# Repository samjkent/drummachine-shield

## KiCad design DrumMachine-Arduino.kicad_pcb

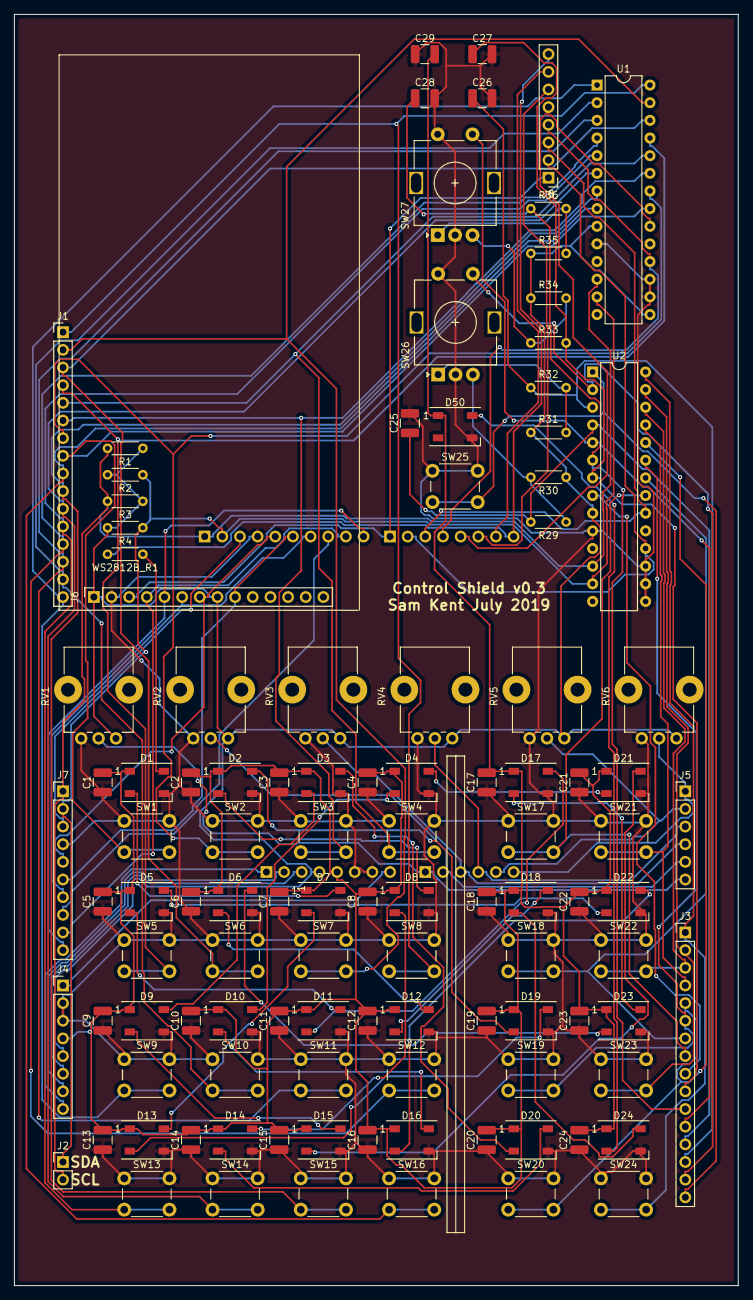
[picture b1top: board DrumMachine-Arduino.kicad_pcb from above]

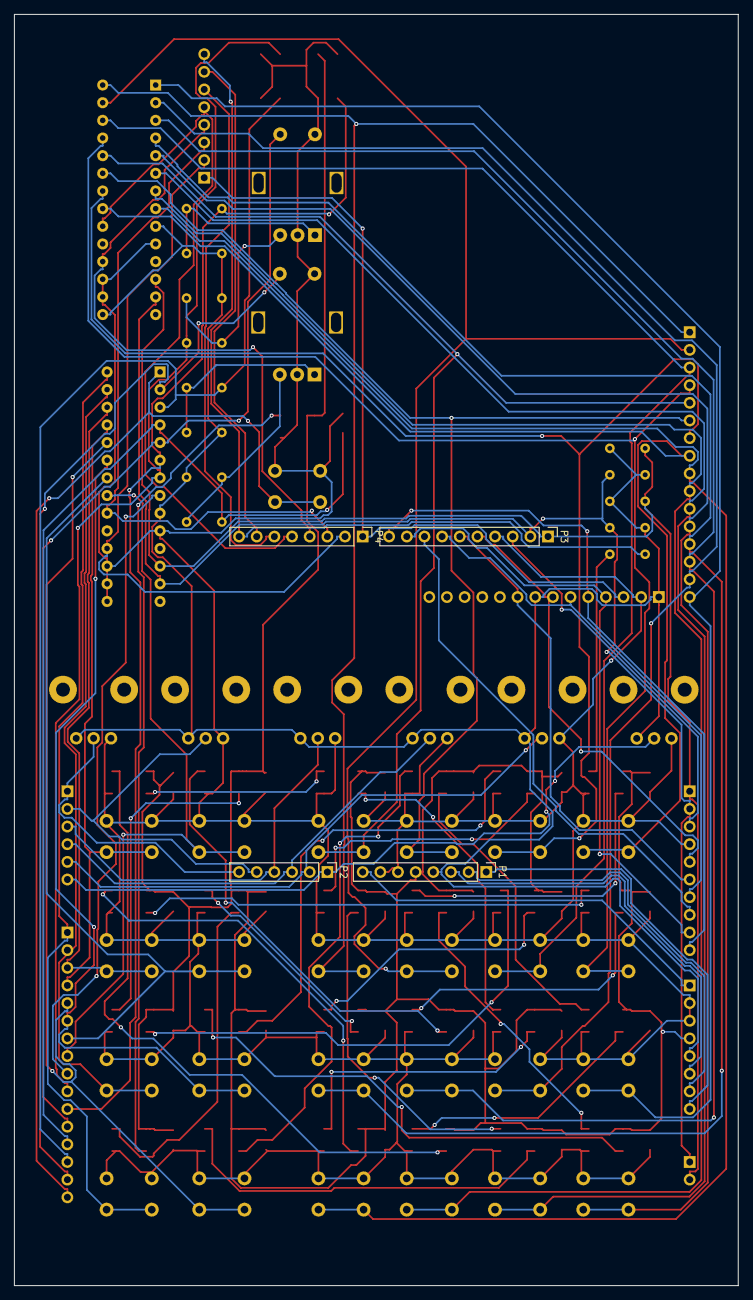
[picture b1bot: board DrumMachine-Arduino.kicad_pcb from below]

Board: 2 copper layers, 104.1 x 182.9 mm, 114 parts (4 on the bottom side), 91 nets.

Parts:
C1, C2, C3, C4, C5, C6, C7, C8, C9, C10, C11, C12, C13, C14, C15, C16, C17, C18, C19, C20, C21, C22, C23, C24, C25, C26, C27, C28, C29: C; C_1210_3225Metric
D1, D2, D3, D4, D5, D6, D7, D8, D9, D10, D11, D12, D13, D14, D15, D16, D17, D18, D19, D20, D21, D22, D23, D24, D50: WS2812B; LED_WS2812B_PLCC4_5.0x5.0mm_P3.2mm
J1, J3: Conn_01x16_Female; PinHeader_1x16_P2.54mm_Vertical
J2: I2C_BUS; PinHeader_1x02_P2.54mm_Vertical
J4, J8: Conn_01x08_Female; PinHeader_1x08_P2.54mm_Vertical
J5: Conn_01x06_Female; PinHeader_1x06_P2.54mm_Vertical
J6: DISPLAY; PinSocket_1x14_P2.54mm_Vertical_Display
J7: Conn_01x10_Female; PinHeader_1x10_P2.54mm_Vertical
P1: Power; PinHeader_1x08_P2.54mm_Vertical
P2: Analog; PinHeader_1x06_P2.54mm_Vertical
P3: Digital; PinHeader_1x10_P2.54mm_Vertical
P4: Digital; PinHeader_1x08_P2.54mm_Vertical
R1, R2, R3, R4, R29, R30, R31, R32, R33, R34, R35, R36: R; R_Axial_DIN0204_L3.6mm_D1.6mm_P5.08mm_Horizontal
RV1, RV2, RV3, RV4, RV5, RV6: R_POT; Potentiometer_Bourns_PTV09A-1_Single_Vertical
SW1, SW2, SW3, SW4, SW5, SW6, SW7, SW8, SW9, SW10, SW11, SW12, SW13, SW14, SW15, SW16, SW17, SW18, SW19, SW20, SW21, SW22, SW23, SW24, SW25: SW_Push; SW_PUSH_6mm_H5mm
SW26, SW27: Rotary_Encoder_Switch; RotaryEncoder_Alps_EC11E-Switch_Vertical_H20mm
U1, U2: MCP23017-E_SP; DIP-28_W7.62mm
WS2812B_R1: R; R_Axial_DIN0204_L3.6mm_D1.6mm_P5.08mm_Horizontal

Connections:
+3V3: J4.5, J6.1, J6.8, P1.4, R1.1, R2.2, R3.1, R4.2, R30.1, R31.1, R34.1, R35.1, RV1.1, RV2.1, RV3.1, RV4.1, RV5.1, RV6.1, U1.9, U1.15, U2.9
+5V: C1.2, C2.2, C3.2, C4.2, C5.2, C6.2, C7.2, C8.2, C9.2, C10.2, C11.2, C12.2, C13.2, C14.2, C15.2, C16.2, C17.2, C18.2, C19.2, C20.2, C21.2, C22.2, C23.2, C24.2, C29.2, D1.1, D2.1, D3.1, D4.1, D5.1, D6.1, D7.1, D8.1, D9.1, D10.1, D11.1, D12.1, D13.1, D14.1, D15.1, D16.1, D17.1, D18.1, D19.1, D20.1, D21.1, D22.1, D23.1, D24.1, D50.1, J4.4, P1.5
/7: J6.3, J8.1, P4.1
/!RESET_0: J8.2, P4.2, U2.18
/!RESET_1: J8.4, P4.4, U1.18
/A0: J5.6, P2.1, RV1.2
/A1: J5.5, P2.2, RV2.2
/A2: J5.4, P2.3, RV3.2
/A3: J5.3, P2.4, RV4.2
/A4: J5.2, P2.5, RV5.2
/A5: J5.1, P2.6, RV6.2
/AREF: J7.3, P3.3
/Ard_Reset: J4.6, P1.3
/DC: J6.5, J7.10, P3.10
/I2C_SCL: J2.2, J7.1, P3.1, R1.2, R3.2, U1.12, U2.12
/I2C_SDA: J2.1, J7.2, P3.2, R2.1, R4.1, U1.13, U2.13
/INTA_0: J8.3, P4.3, U2.20
/INTA_1: J8.5, P4.5, U1.20
/IOREF: J4.7, P1.2
/MISO: J6.9, J7.6, P3.6
/MOSI: J6.6, J7.7, P3.7
/RESET: J6.4, J7.9, P3.9
/SCK: J6.7, J7.5, P3.5
/U1_GPA0: J1.8, SW1.2, U1.21
/U1_GPA1: J1.7, SW2.2, U1.22
/U1_GPA2: J1.6, SW3.2, U1.23
/U1_GPA3: J1.5, SW4.2, U1.24
/U1_GPA4: J1.4, SW5.2, U1.25
/U1_GPA5: J1.3, SW6.2, U1.26
/U1_GPA6: J1.2, SW7.2, U1.27
/U1_GPA7: J1.1, SW8.2, U1.28
/U1_GPB0: J1.16, SW9.2, U1.1
/U1_GPB1: J1.15, SW10.2, U1.2
/U1_GPB2: J1.14, SW11.2, U1.3
/U1_GPB3: J1.13, SW12.2, U1.4
/U1_GPB4: J1.12, SW13.2, U1.5
/U1_GPB5: J1.11, SW14.2, U1.6
/U1_GPB6: J1.10, SW15.2, U1.7
/U1_GPB7: J1.9, SW16.2, U1.8
/U2_GPA0: J3.8, SW17.2, U2.21
/U2_GPA1: J3.7, SW18.2, U2.22
/U2_GPA2: J3.6, SW19.2, U2.23
/U2_GPA3: J3.5, SW20.2, U2.24
/U2_GPA4: J3.4, SW21.2, U2.25
/U2_GPA5: J3.3, SW22.2, U2.26
/U2_GPA6: J3.2, SW23.2, U2.27
/U2_GPA7: J3.1, SW24.2, U2.28
/U2_GPB0: J3.16, SW25.2, U2.1
/U2_GPB1: J3.15, SW26.S1, U2.2
/U2_GPB2: C26.1, J3.14, R32.1, U2.3
/U2_GPB3: C25.1, J3.13, R29.2, U2.4
/U2_GPB4: J3.12, SW27.S1, U2.5
/U2_GPB5: C28.1, J3.11, R36.1, U2.6
/U2_GPB6: C27.1, J3.10, R33.2, U2.7
/U2_GPB7: J3.9, U2.8
/Vin: J4.1, P1.8
/WS2812B: J8.8, P4.8, WS2812B_R1.2
GND: C1.1, C2.1, C3.1, C4.1, C5.1, C6.1, C7.1, C8.1, C9.1, C10.1, C11.1, C12.1, C13.1, C14.1, C15.1, C16.1, C17.1, C18.1, C19.1, C20.1, C21.1, C22.1, C23.1, C24.1, C25.2, C26.2, C27.2, C28.2, C29.1, D1.3, D2.3, D3.3, D4.3, D5.3, D6.3, D7.3, D8.3, D9.3, D10.3, D11.3, D12.3, D13.3, D14.3, D15.3, D16.3, D17.3, D18.3, D19.3, D20.3, D21.3, D22.3, D23.3, D24.3, D50.3, J4.2, J4.3, J6.2, J7.4, P1.6, P1.7, P3.4, RV1.3, RV2.3, RV3.3, RV4.3, RV5.3, RV6.3, SW1.1, SW2.1, SW3.1, SW4.1, SW5.1, SW6.1, SW7.1, SW8.1, SW9.1, SW10.1, SW11.1, SW12.1, SW13.1, SW14.1, SW15.1, SW16.1, SW17.1, SW18.1, SW19.1, SW20.1, SW21.1, SW22.1, SW23.1, SW24.1, SW25.1, SW26.C, SW26.S2, SW27.C, SW27.S2, U1.10, U1.16, U1.17, U2.10, U2.15, U2.16, U2.17
unnamed: D1.2, D7.4
unnamed: D1.4, WS2812B_R1.1
unnamed: D2.2, D8.4
unnamed: D3.2, D9.4
unnamed: D10.2, D16.4
unnamed: D4.2, D10.4
unnamed: D11.2, D17.4
unnamed: D5.2, D11.4
unnamed: D12.2, D18.4
unnamed: D6.2, D12.4
unnamed: D13.2, D19.4
unnamed: D7.2, D13.4
unnamed: D14.2, D20.4
unnamed: D8.2, D14.4
unnamed: D15.2, D21.4
unnamed: D9.2, D15.4
unnamed: D16.2, D22.4
unnamed: D17.2, D23.4
unnamed: D18.2, D24.4
unnamed: D2.4, D19.2
unnamed: D3.4, D20.2
unnamed: D4.4, D21.2
unnamed: D5.4, D22.2
unnamed: D6.4, D23.2
unnamed: D24.2, D50.4
unnamed: J4.8, P1.1
unnamed: J7.8, P3.8
unnamed: J8.6, P4.6
unnamed: J8.7, P4.7
unnamed: R29.1, R30.2, SW26.B
unnamed: R31.2, R32.2, SW26.A
unnamed: R33.1, R34.2, SW27.B
unnamed: R35.2, R36.2, SW27.A
